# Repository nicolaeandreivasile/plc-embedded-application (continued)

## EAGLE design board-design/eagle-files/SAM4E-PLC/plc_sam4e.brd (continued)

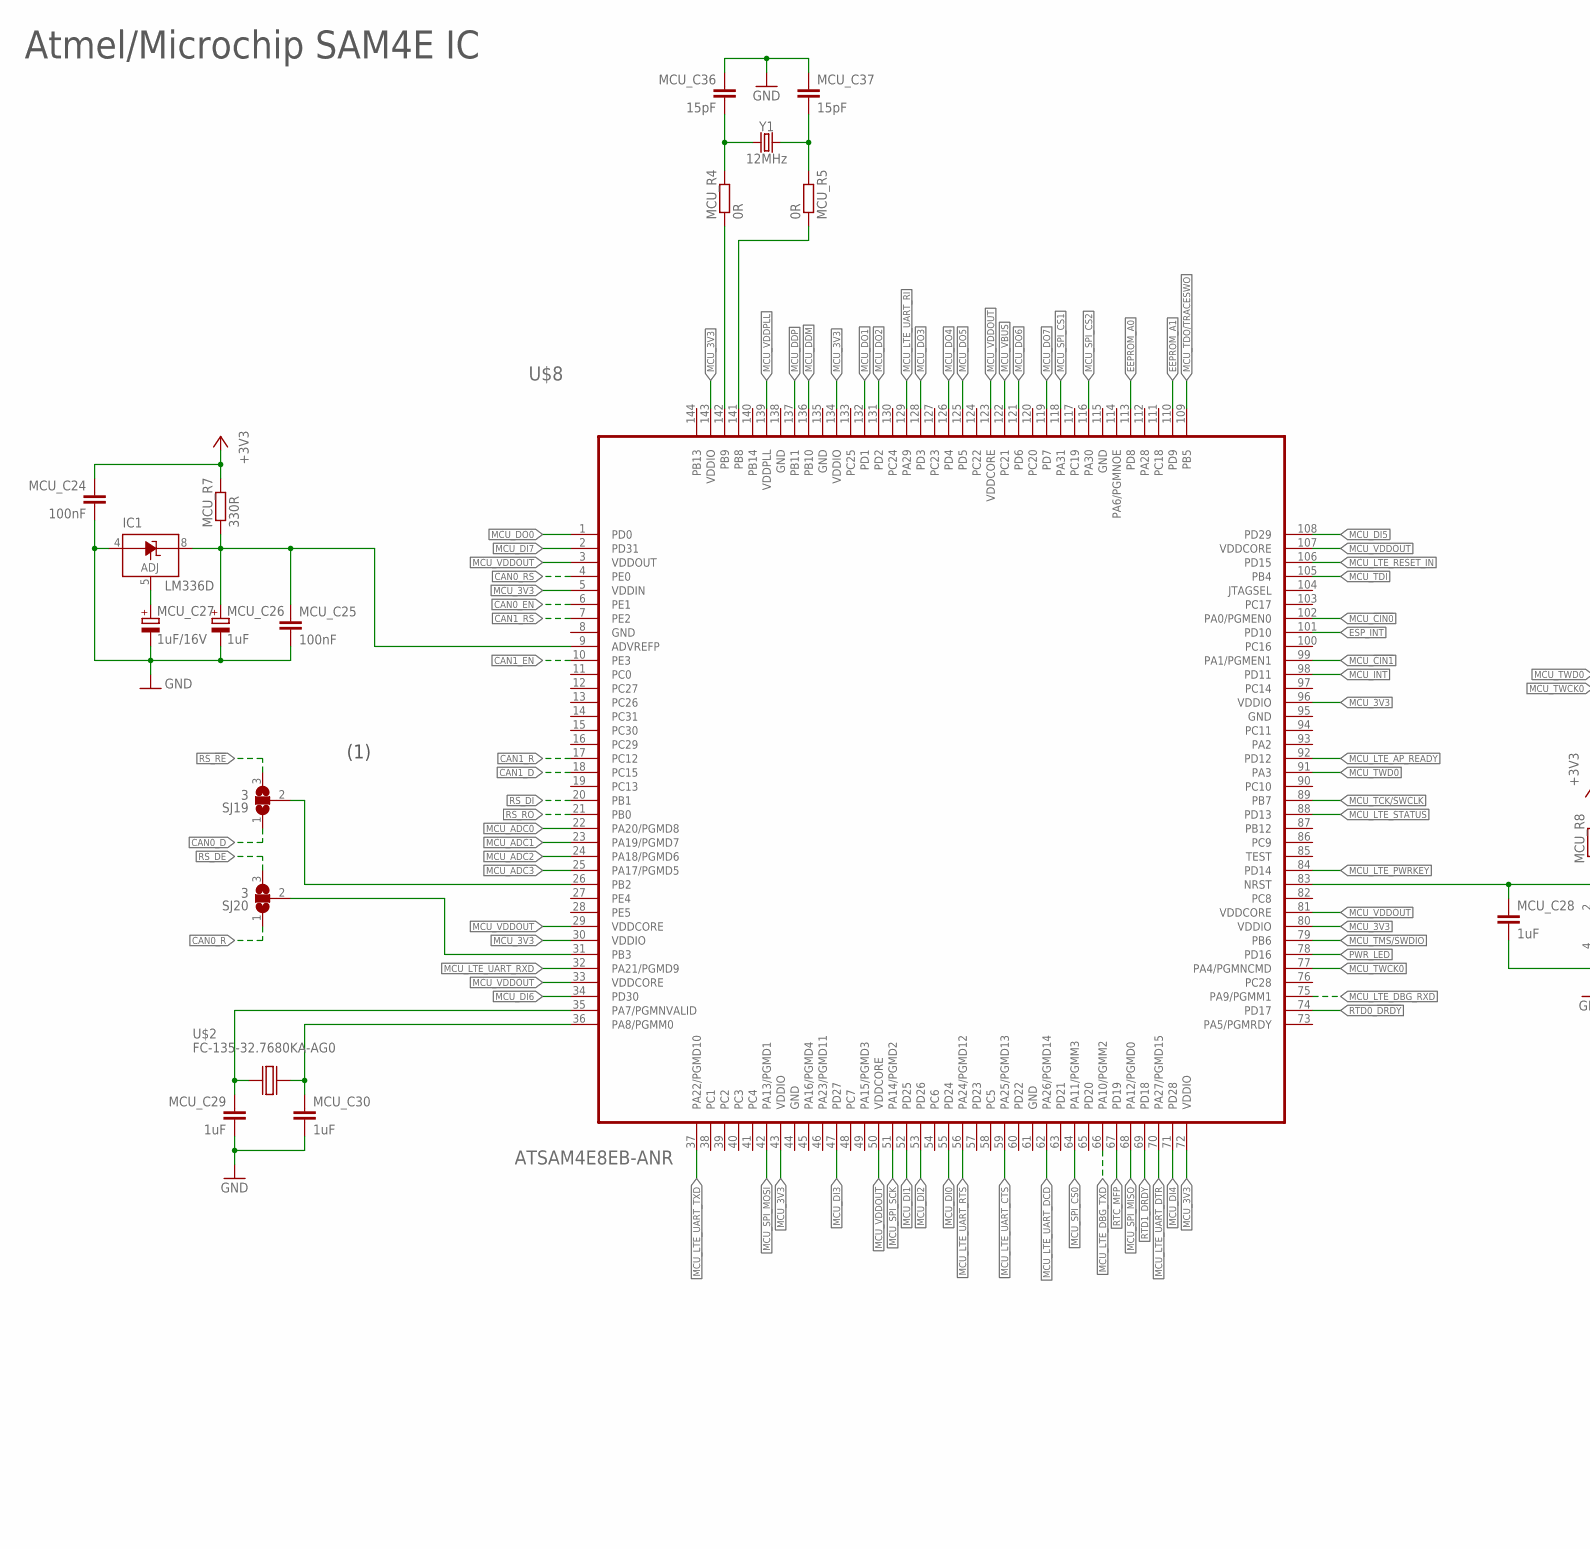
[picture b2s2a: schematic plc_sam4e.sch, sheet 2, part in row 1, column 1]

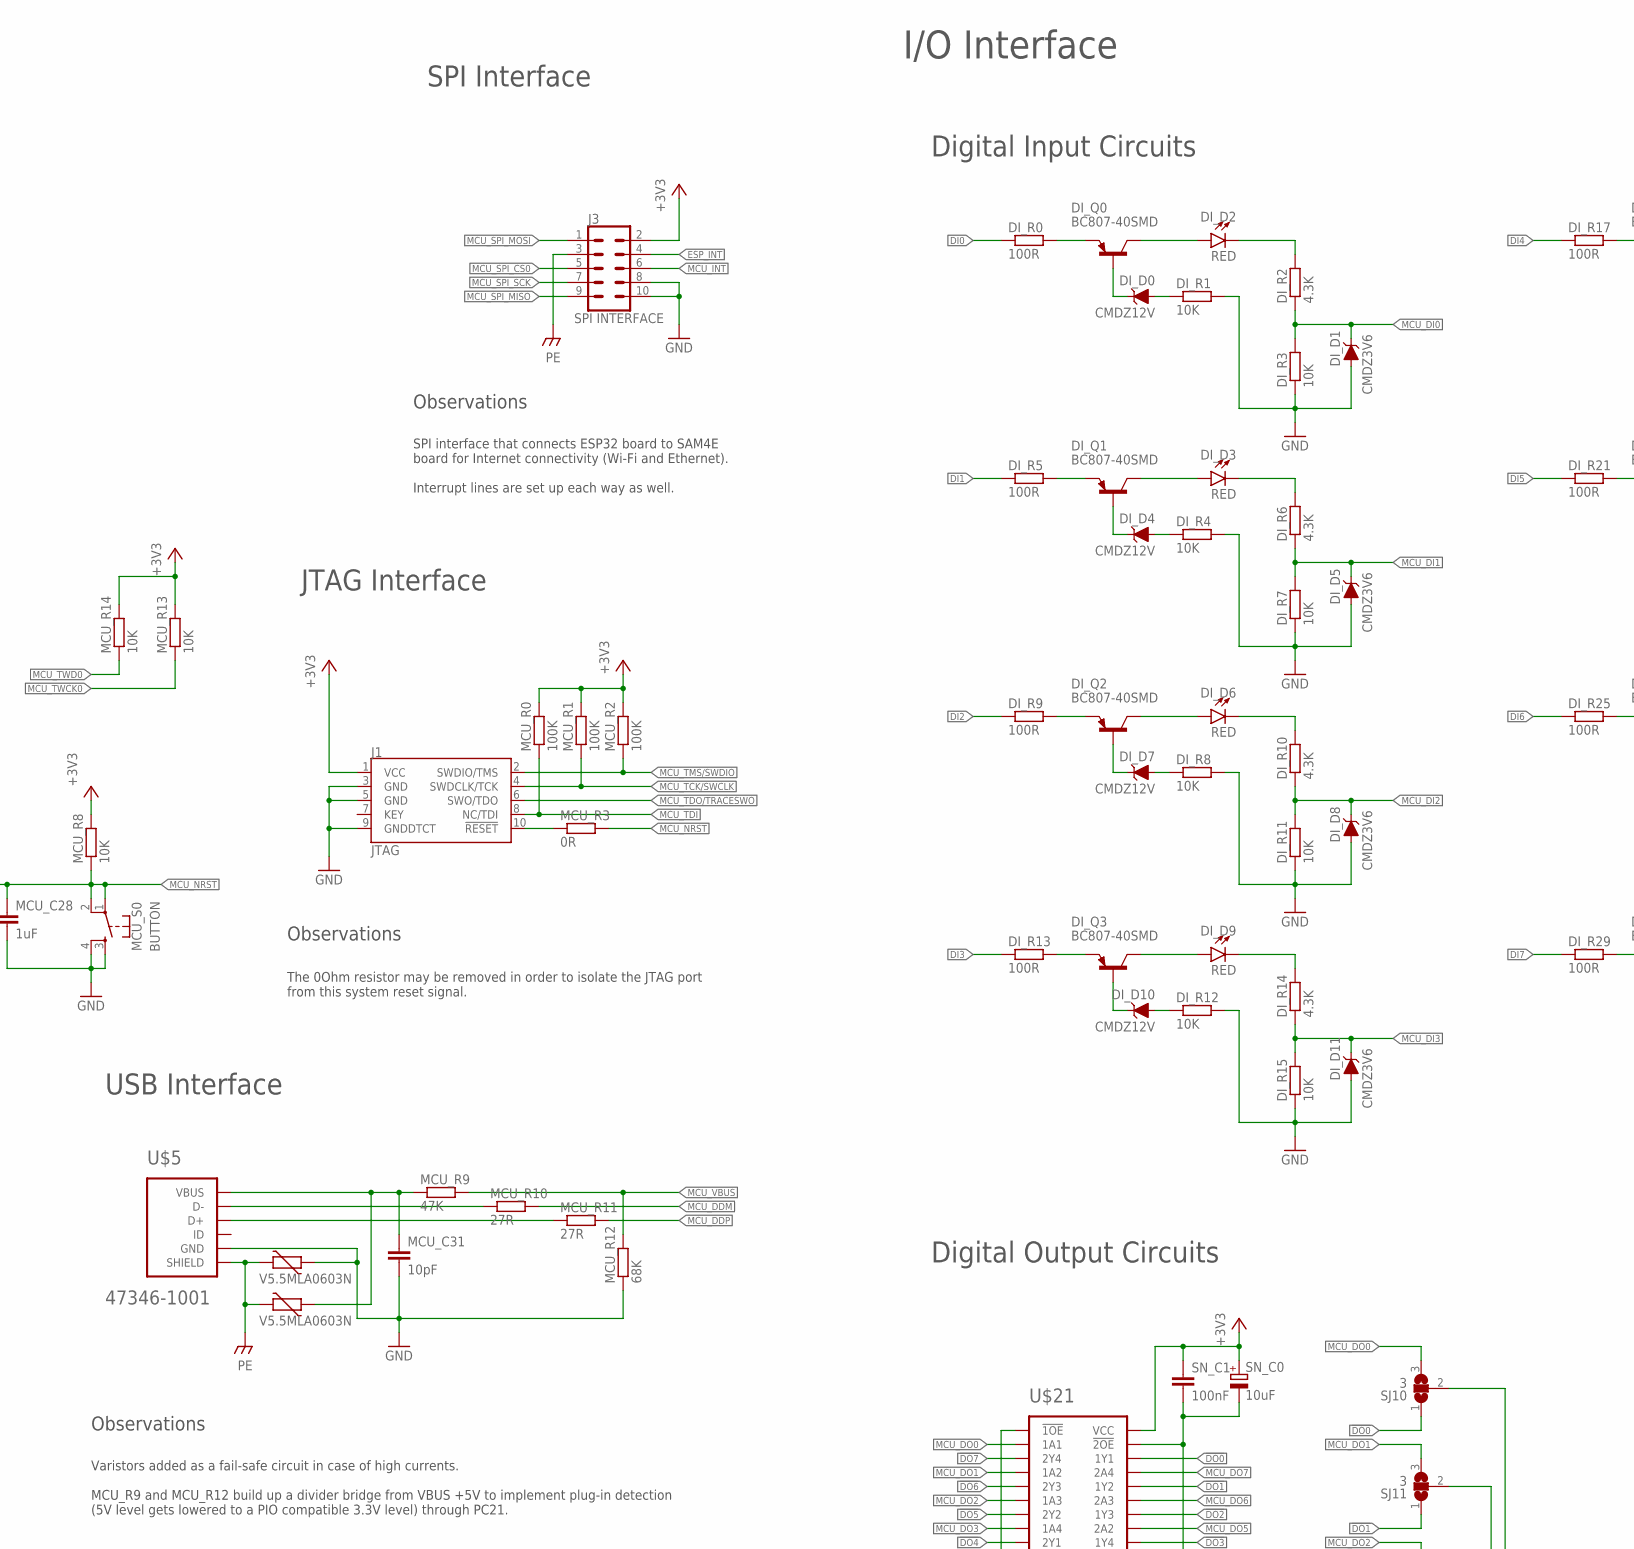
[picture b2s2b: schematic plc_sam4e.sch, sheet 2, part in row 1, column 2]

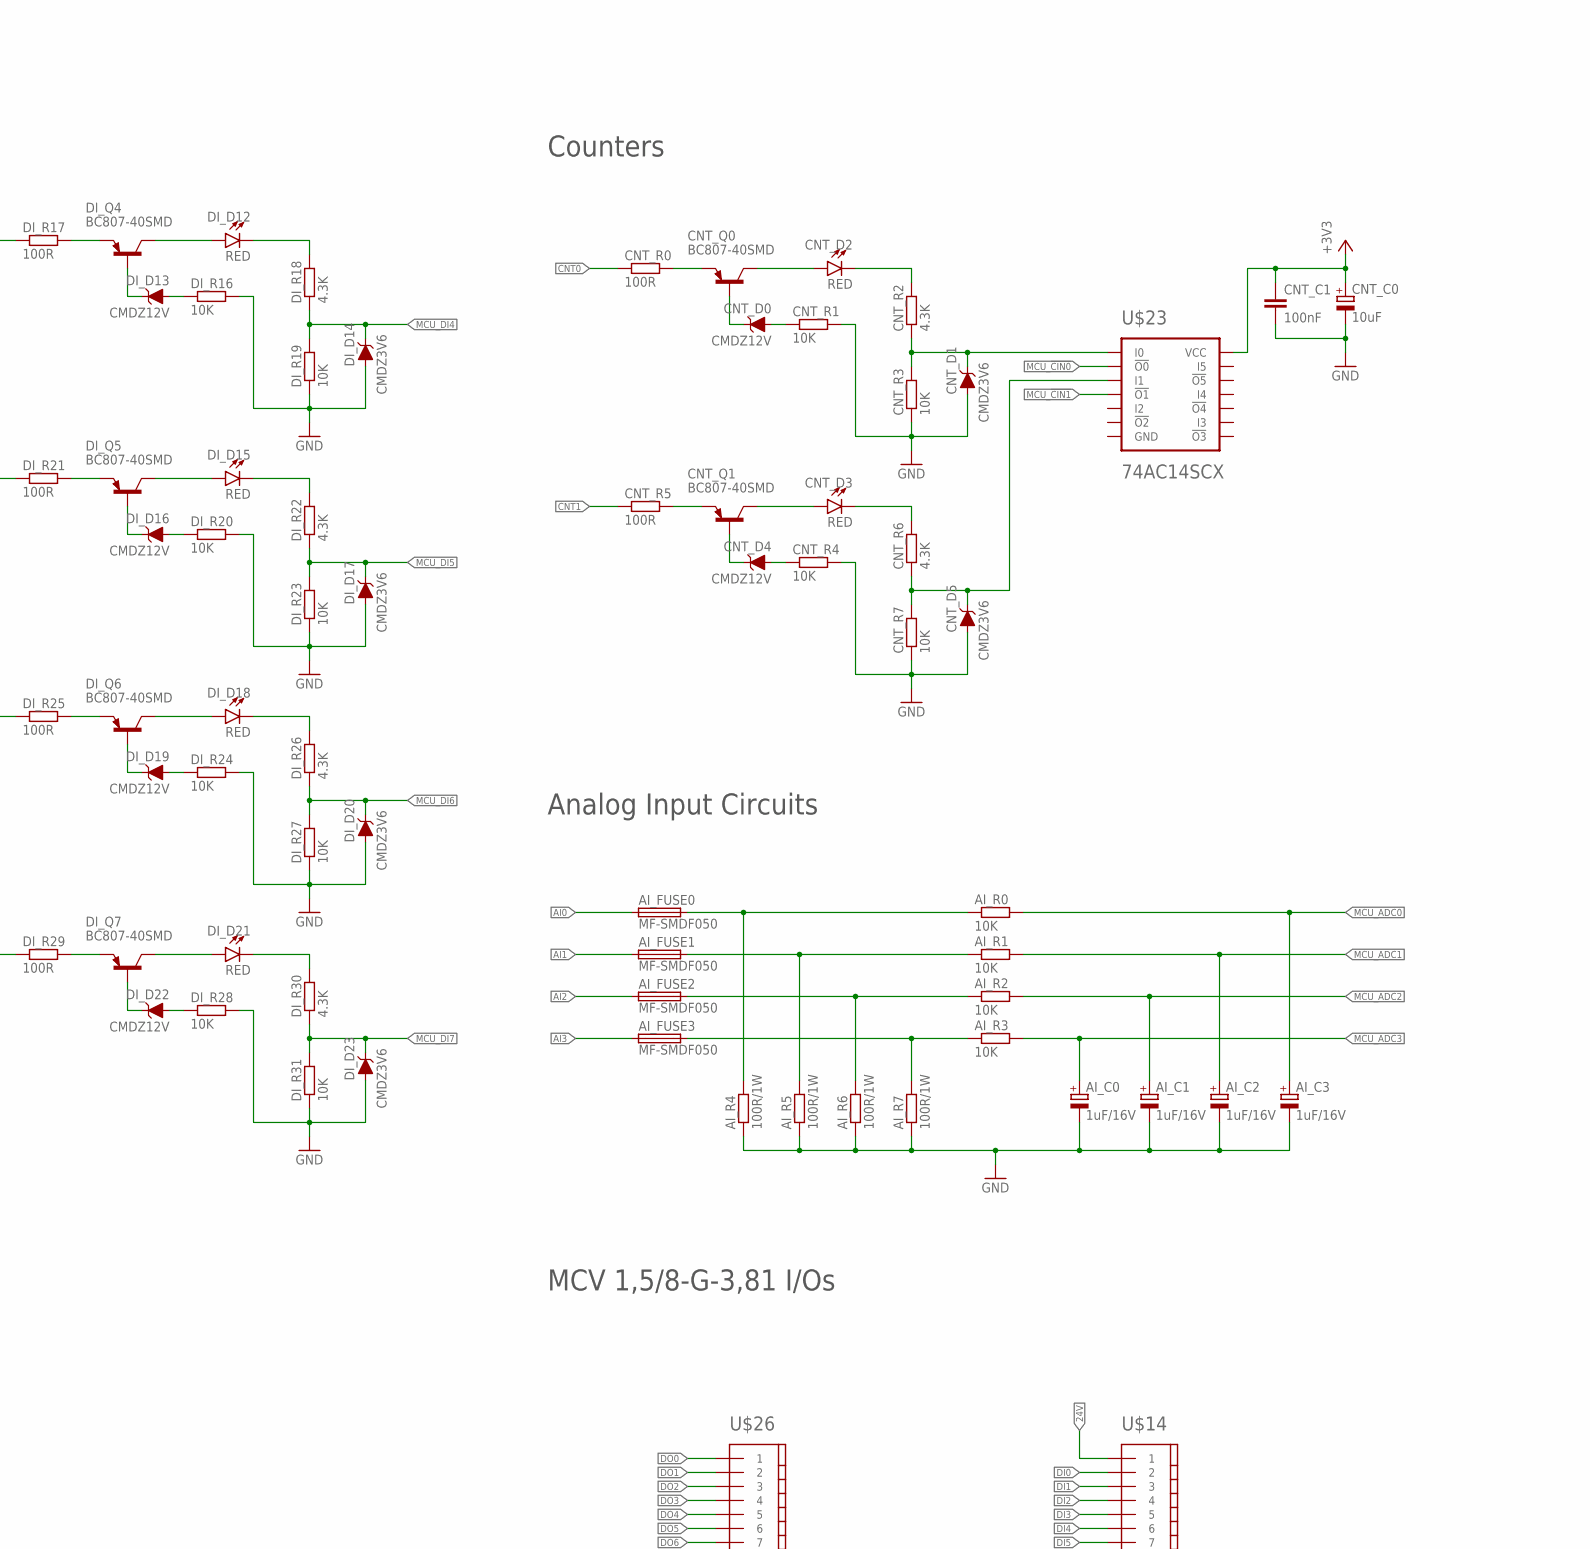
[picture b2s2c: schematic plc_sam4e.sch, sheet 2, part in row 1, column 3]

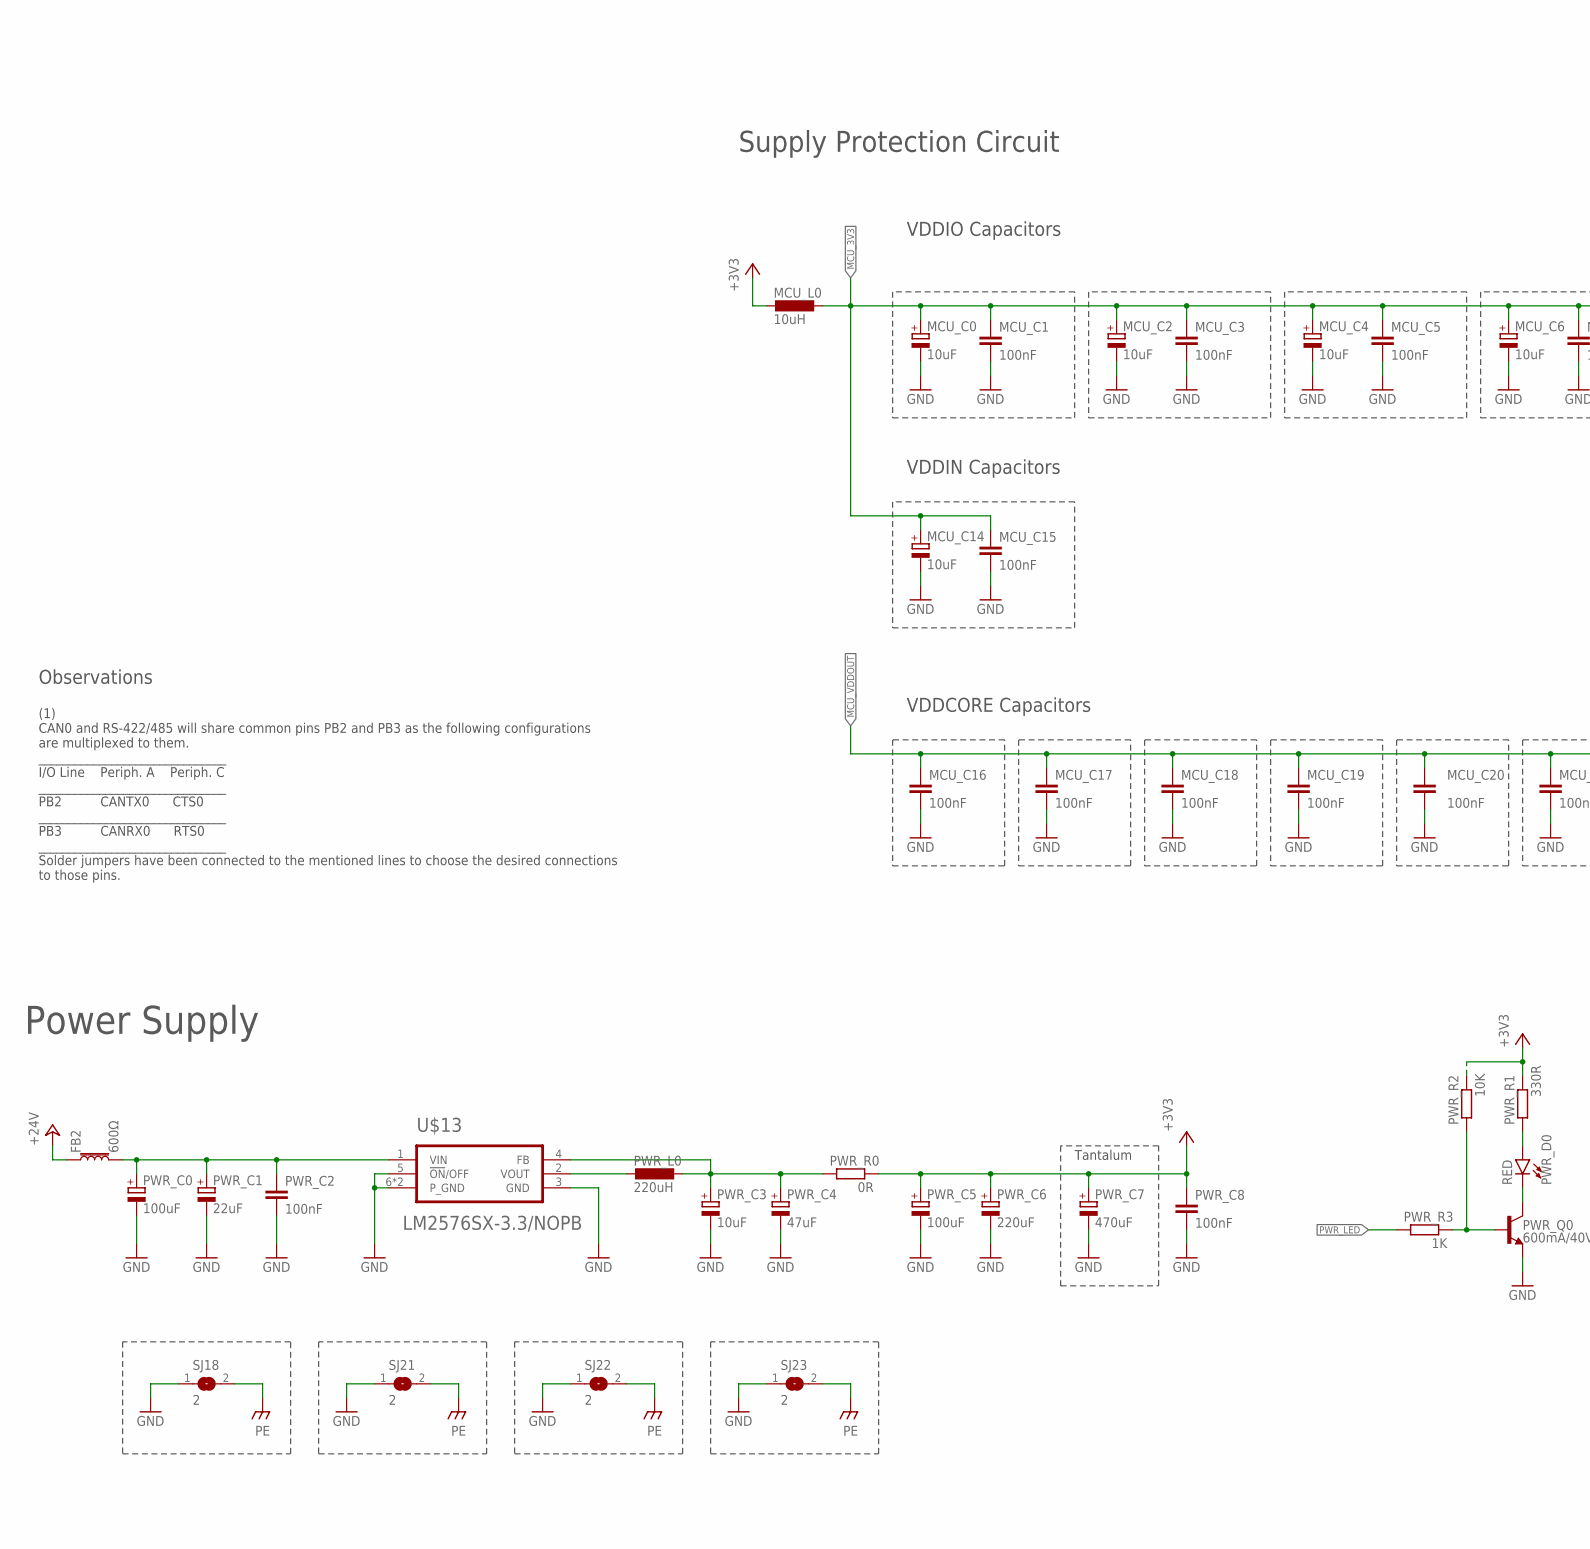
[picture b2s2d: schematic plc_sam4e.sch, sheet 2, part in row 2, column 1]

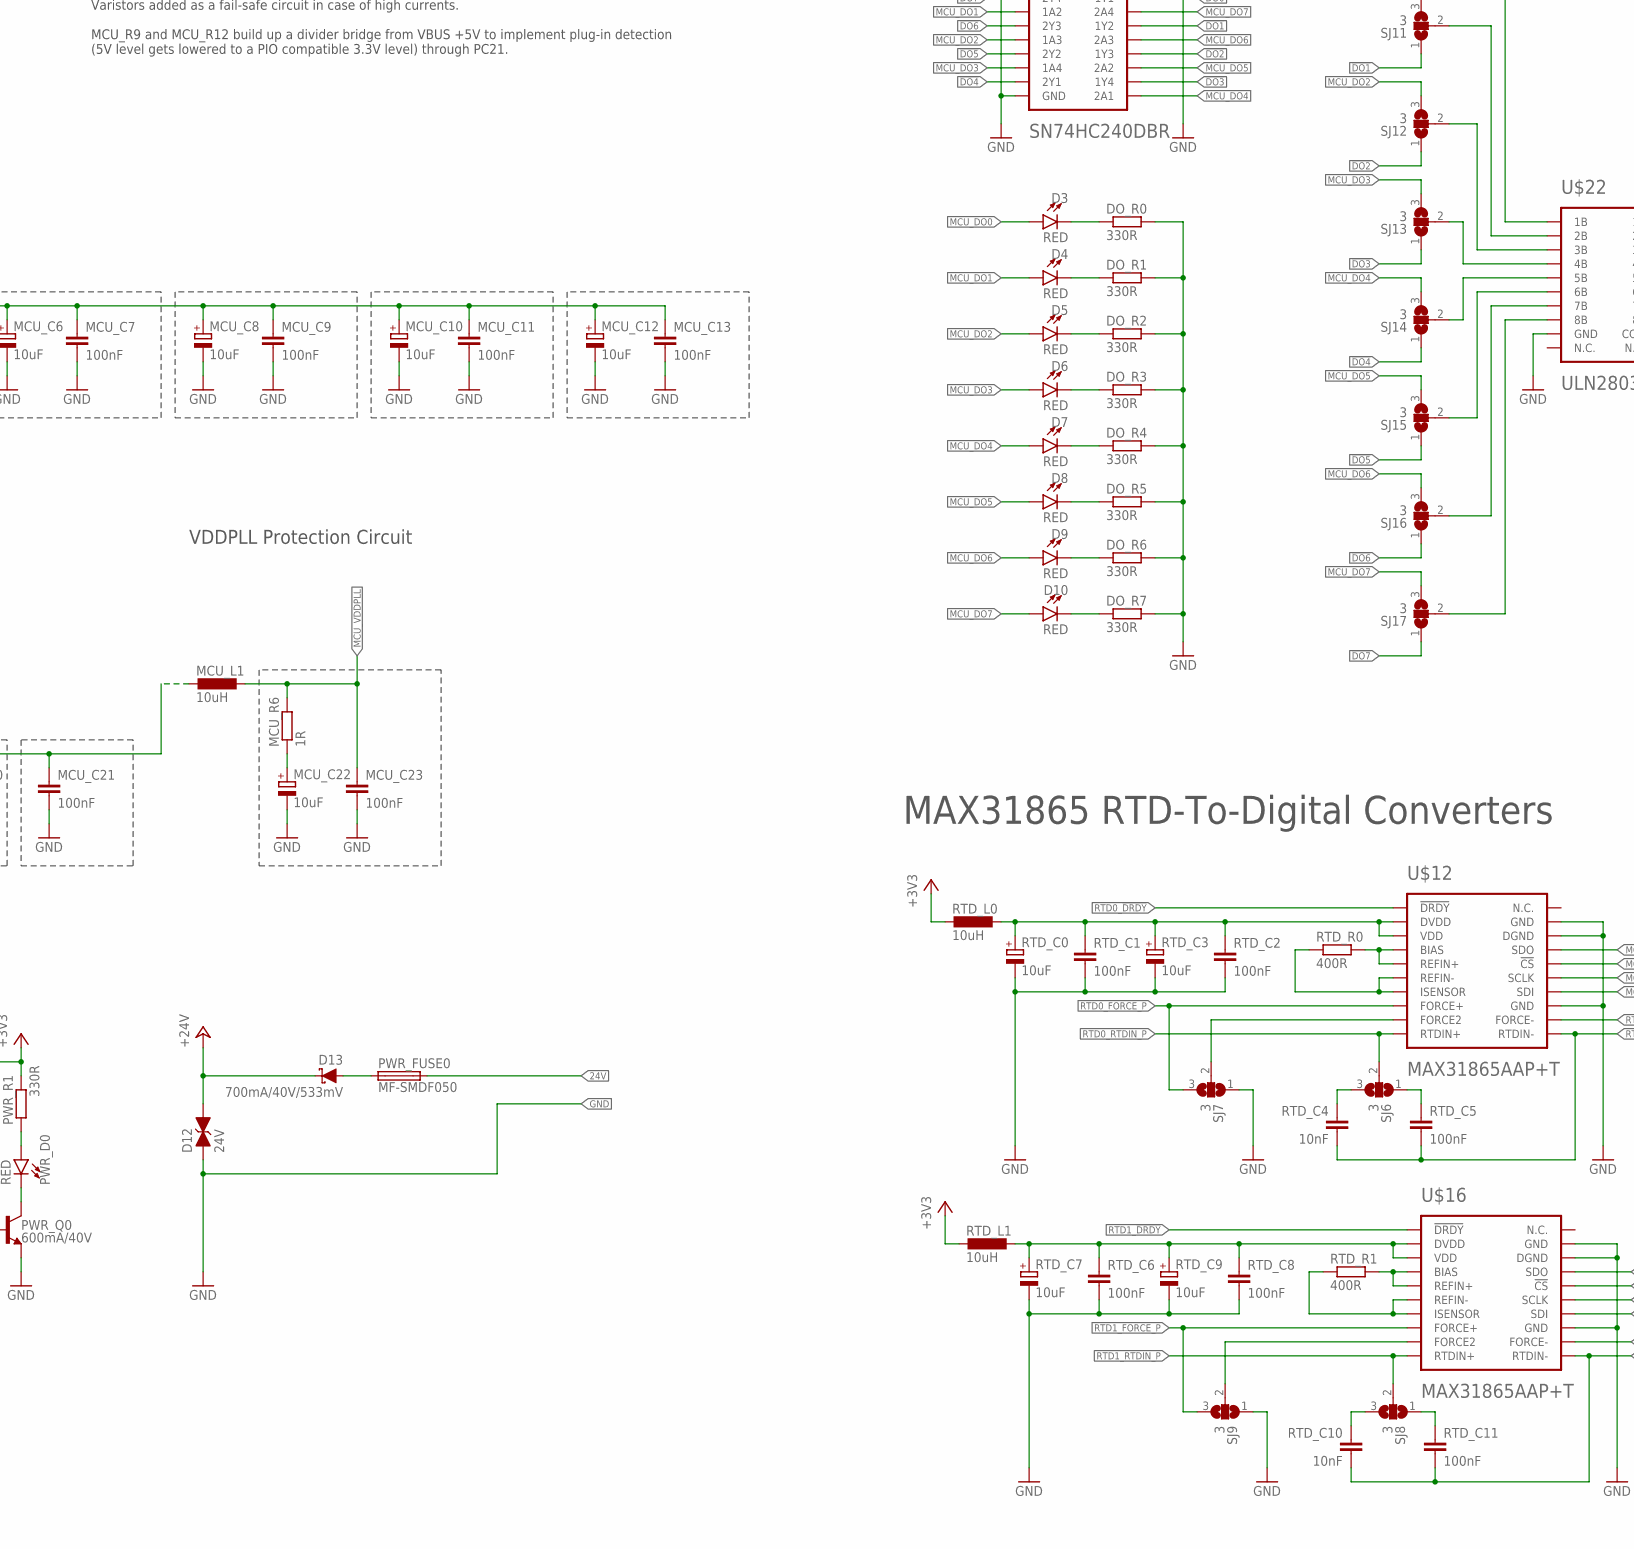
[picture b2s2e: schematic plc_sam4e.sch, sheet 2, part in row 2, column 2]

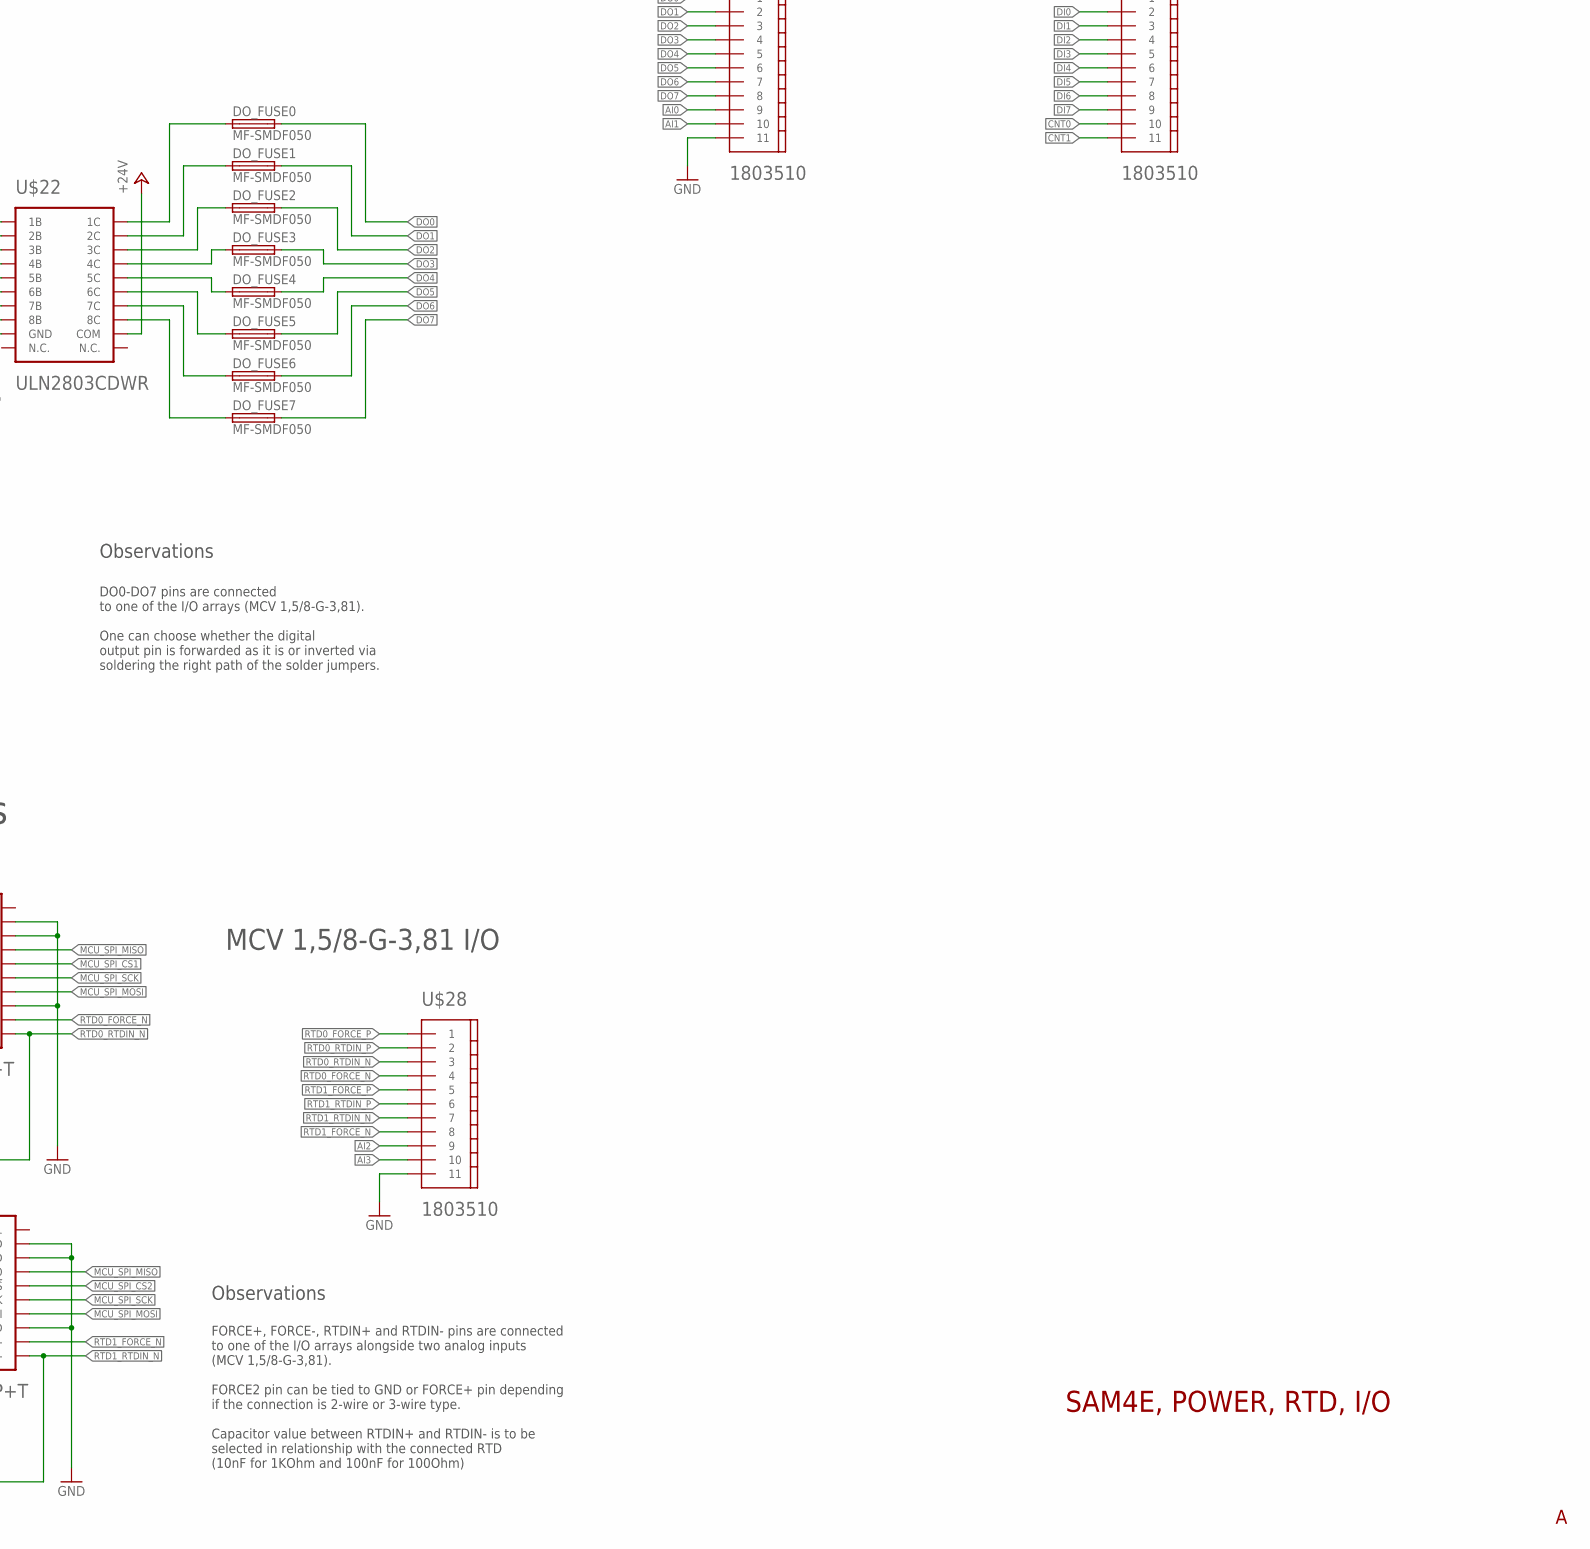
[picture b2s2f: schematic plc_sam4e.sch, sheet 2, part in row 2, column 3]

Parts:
AI_C0, AI_C1, AI_C2, AI_C3: 1uF/16V; SMC_B
AI_FUSE0, AI_FUSE1, AI_FUSE2, AI_FUSE3: MF-SMDF050
AI_R0, AI_R1, AI_R2, AI_R3: 10K; R0402
AI_R4, AI_R5, AI_R6, AI_R7: 100R/1W; R0402
CNT_C0: 10uF; SMC_B
CNT_C1: 100nF; C0402
CNT_D0, CNT_D4: CMDZ12V; SOD-323
CNT_D1, CNT_D5: CMDZ3V6; SOD-323
CNT_D2, CNT_D3: RED; LED-1206
CNT_Q0, CNT_Q1: BC807-40SMD; SOT23-BEC
CNT_R0, CNT_R5: 100R; R0402
CNT_R1, CNT_R3, CNT_R4, CNT_R7: 10K; R0402
CNT_R2, CNT_R6: 4.3K; R0402
D3, D4, D5, D6, D7, D8, D9, D10: RED; LED-1206
D12: 24V; 0603
D13: 700mA/40V/533mV; SOT23-3
DI_D0, DI_D4, DI_D7, DI_D10, DI_D13, DI_D16, DI_D19, DI_D22: CMDZ12V; SOD-323
DI_D1, DI_D5, DI_D8, DI_D11, DI_D14, DI_D17, DI_D20, DI_D23: CMDZ3V6; SOD-323
DI_D2, DI_D3, DI_D6, DI_D9, DI_D12, DI_D15, DI_D18, DI_D21: RED; LED-1206
DI_Q0, DI_Q1, DI_Q2, DI_Q3, DI_Q4, DI_Q5, DI_Q6, DI_Q7: BC807-40SMD; SOT23-BEC
DI_R0, DI_R5, DI_R9, DI_R13, DI_R17, DI_R21, DI_R25, DI_R29: 100R; R0402
DI_R1, DI_R3, DI_R4, DI_R7, DI_R8, DI_R11, DI_R12, DI_R15, DI_R16, DI_R19, DI_R20, DI_R23, DI_R24, DI_R27, DI_R28, DI_R31: 10K; R0402
DI_R2, DI_R6, DI_R10, DI_R14, DI_R18, DI_R22, DI_R26, DI_R30: 4.3K; R0402
DO_FUSE0, DO_FUSE1, DO_FUSE2, DO_FUSE3, DO_FUSE4, DO_FUSE5, DO_FUSE6, DO_FUSE7: MF-SMDF050
DO_R0, DO_R1, DO_R2, DO_R3, DO_R4, DO_R5, DO_R6, DO_R7: 330R; R0402
FB2: 600Ω; 0805
IC1: LM336D; SO08
J1: JTAG; 2X5-SMD-UNSHROUDED
J3: SPI INTERFACE; 2X5-SHROUDED_SMD
MCU_C0, MCU_C2, MCU_C4, MCU_C6, MCU_C8, MCU_C10, MCU_C12, MCU_C14, MCU_C22: 10uF; SMC_B
MCU_C1, MCU_C3, MCU_C5, MCU_C7, MCU_C9, MCU_C11, MCU_C13, MCU_C15, MCU_C16, MCU_C17, MCU_C18, MCU_C19, MCU_C20, MCU_C21, MCU_C23, MCU_C24, MCU_C25: 100nF; C0402
MCU_C26: 1uF; SMC_B
MCU_C27: 1uF/16V; SMC_B
MCU_C28, MCU_C29, MCU_C30: 1uF; C0402
MCU_C31: 10pF; C0402
MCU_C36, MCU_C37: 15pF; C0402
MCU_L0, MCU_L1: 10uH; L1812
MCU_R0, MCU_R1, MCU_R2: 100K; R0402
MCU_R3, MCU_R4, MCU_R5: 0R; R0402
MCU_R6: 1R; R0402
MCU_R7: 330R; R0402
MCU_R8, MCU_R13, MCU_R14: 10K; R0402
MCU_R9: 47K; R0402
MCU_R10, MCU_R11: 27R; R0402
MCU_R12: 68K; R0402
MCU_S0: BUTTON; TACTILE_SWITCH_SMD_4.6X2.8MM
MCU_VAR0, MCU_VAR1: V5.5MLA0603N; CT/CN0603
PWR_C0, PWR_C5: 100uF; SMC_B
PWR_C1: 22uF; SMC_B
PWR_C2, PWR_C8: 100nF; C0402
PWR_C3: 10uF; SMC_B
PWR_C4: 47uF; SMC_B
PWR_C6: 220uF; SMC_B
PWR_C7: 470uF; SMC_B
PWR_D0: RED; LED-1206
PWR_FUSE0: MF-SMDF050
PWR_L0: 220uH; L1812
PWR_Q0: 600mA/40V; SOT23-3
PWR_R0: 0R; R0402
PWR_R1: 330R; R0402
PWR_R2: 10K; R0402
PWR_R3: 1K; R0402
RTD_C0, RTD_C3, RTD_C7, RTD_C9: 10uF; SMC_B
RTD_C1, RTD_C2, RTD_C5, RTD_C6, RTD_C8, RTD_C11: 100nF; C0402
RTD_C4, RTD_C10: 10nF; C0402
RTD_L0, RTD_L1: 10uH; L1812
RTD_R0, RTD_R1: 400R; R0402
SJ6, SJ7, SJ8, SJ9, SJ10, SJ11, SJ12, SJ13, SJ14, SJ15, SJ16, SJ17, SJ19, SJ20: 3; SJ_2
SJ18, SJ21, SJ22, SJ23: 2; SJ
SN_C0: 10uF; SMC_B
SN_C1: 100nF; C0402
U$2: FC-135-32.7680KA-AG0; 3.2X1.5MM
U$5: 47346-1001
U$8: ATSAM4E8EB-ANR; LQFP-144
U$12, U$16: MAX31865AAP+T; TSSOP-20
U$13: LM2576SX-3.3/NOPB; TO-263-5
U$14, U$26, U$28: 1803510
U$21: SN74HC240DBR; SSOP-20
U$22: ULN2803CDWR; SOIC-20
U$23: 74AC14SCX; SOIC-14
Y1: 12MHz; CRYSTAL-SMD-3.2X2.5MM

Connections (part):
24V: PWR_FUSE0.2, U$14.1; also elsewhere on the board
!DO0: SJ10.1, U$21.18 (1Y1)
!DO1: SJ11.1, U$21.16 (1Y2)
!DO2: SJ12.1, U$21.14 (1Y3)
!DO3: SJ13.1, U$21.12 (1Y4)
!DO4: SJ14.1, U$21.9 (2Y1)
!DO5: SJ15.1, U$21.7 (2Y2)
!DO6: SJ16.1, U$21.5 (2Y3)
!DO7: SJ17.1, U$21.3 (2Y4)
+3V3: CNT_C0.+, CNT_C1.1, J1.1 (VCC), J3.2, MCU_C24.1, MCU_L0.2, MCU_R0.2, MCU_R1.2, MCU_R2.2, MCU_R7.2, MCU_R8.2, MCU_R13.2, MCU_R14.2, PWR_C5.+, PWR_C6.+, PWR_C7.+, PWR_C8.1, PWR_R0.2, PWR_R1.2, PWR_R2.2, RTD_L0.2, RTD_L1.2, SN_C0.+, SN_C1.1, U$21.20 (VCC), U$23.14 (VCC); also elsewhere on the board
+24V: D12.2 (C), D13.3 (C), FB2.1, U$22.12 (COM)
AI0: AI_FUSE0.1, U$26.9
AI1: AI_FUSE1.1, U$26.10
AI2: AI_FUSE2.1, U$28.9
AI3: AI_FUSE3.1, U$28.10
CAN0_D: SJ19.1; also elsewhere on the board
CAN0_EN: U$8.6 (PE1); also elsewhere on the board
CAN0_R: SJ20.1; also elsewhere on the board
CAN0_RS: U$8.4 (PE0); also elsewhere on the board
CAN1_D: U$8.18 (PC15); also elsewhere on the board
CAN1_EN: U$8.10 (PE3); also elsewhere on the board
CAN1_R: U$8.17 (PC12); also elsewhere on the board
CAN1_RS: U$8.7 (PE2); also elsewhere on the board
CNT0: CNT_R0.1, U$14.10
CNT1: CNT_R5.1, U$14.11
DI0: DI_R0.1, U$14.2
DI1: DI_R5.1, U$14.3
DI2: DI_R9.1, U$14.4
DI3: DI_R13.1, U$14.5
DI4: DI_R17.1, U$14.6
DI5: DI_R21.1, U$14.7
DI6: DI_R25.1, U$14.8
DI7: DI_R29.1, U$14.9
DO0: DO_FUSE0.2, U$26.1
DO1: DO_FUSE1.2, U$26.2
DO2: DO_FUSE2.2, U$26.3
DO3: DO_FUSE3.2, U$26.4
DO4: DO_FUSE4.2, U$26.5
DO5: DO_FUSE5.2, U$26.6
DO6: DO_FUSE6.2, U$26.7
DO7: DO_FUSE7.2, U$26.8
EEPROM_A0: U$8.113 (PD8); also elsewhere on the board
EEPROM_A1: U$8.110 (PD9); also elsewhere on the board
ESP_INT: J3.4, U$8.101 (PD10)
GND: AI_C0.-, AI_C1.-, AI_C2.-, AI_C3.-, AI_R4.1, AI_R5.1, AI_R6.1, AI_R7.1, CNT_C0.-, CNT_C1.2, CNT_D1.A, CNT_D5.A, CNT_R1.2, CNT_R3.1, CNT_R4.2, CNT_R7.1, D12.1 (A), DI_D1.A, DI_D5.A, DI_D8.A, DI_D11.A, DI_D14.A, DI_D17.A, DI_D20.A, DI_D23.A, DI_R1.2, DI_R3.1, DI_R4.2, DI_R7.1, DI_R8.2, DI_R11.1, DI_R12.2, DI_R15.1, DI_R16.2, DI_R19.1, DI_R20.2, DI_R23.1, DI_R24.2, DI_R27.1, DI_R28.2, DI_R31.1, DO_R0.2, DO_R1.2, DO_R2.2, DO_R3.2, DO_R4.2, DO_R5.2, DO_R6.2, DO_R7.2, IC1.4 (A), J1.3 (GND), J1.5 (GND), J1.9 (GNDDTCT), J3.8, J3.10, MCU_C0.-, MCU_C1.2, MCU_C2.-, MCU_C3.2, MCU_C4.-, MCU_C5.2, MCU_C6.-, MCU_C7.2, MCU_C8.-, MCU_C9.2, MCU_C10.-, MCU_C11.2, MCU_C12.-, MCU_C13.2, MCU_C14.-, MCU_C15.2, MCU_C16.2, MCU_C17.2, MCU_C18.2, MCU_C19.2, MCU_C20.2, MCU_C21.2, MCU_C22.-, MCU_C23.2, MCU_C24.2, MCU_C25.2, MCU_C26.-, MCU_C27.-, MCU_C28.2, MCU_C29.2, MCU_C30.2, MCU_C31.2, MCU_C36.1, MCU_C37.1, MCU_R12.1, MCU_S0.3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; also elsewhere on the board
MCU_3V3: MCU_C0.+, MCU_C1.1, MCU_C2.+, MCU_C3.1, MCU_C4.+, MCU_C5.1, MCU_C6.+, MCU_C7.1, MCU_C8.+, MCU_C9.1, MCU_C10.+, MCU_C11.1, MCU_C12.+, MCU_C13.1, MCU_C14.+, MCU_C15.1, MCU_L0.1, U$8.5 (VDDIN), U$8.30 (VDDIO), U$8.43 (VDDIO), U$8.72 (VDDIO), U$8.80 (VDDIO), U$8.96 (VDDIO), U$8.134 (VDDIO), U$8.143 (VDDIO)
MCU_!CIN0: U$8.102 (PA0/PGMEN0), U$23.2 (!O0)
MCU_!CIN1: U$8.99 (PA1/PGMEN1), U$23.4 (!O1)
MCU_ADC0: AI_C3.+, AI_R0.2, U$8.22 (PA20/PGMD8)
MCU_ADC1: AI_C2.+, AI_R1.2, U$8.23 (PA19/PGMD7)
MCU_ADC2: AI_C1.+, AI_R2.2, U$8.24 (PA18/PGMD6)
MCU_ADC3: AI_C0.+, AI_R3.2, U$8.25 (PA17/PGMD5)
MCU_ADVREFP: IC1.8 (C), MCU_C25.1, MCU_C26.+, MCU_R7.1, U$8.9 (ADVREFP)
MCU_DDM: MCU_R10.2, U$8.136 (PB10)
MCU_DDP: MCU_R11.2, U$8.137 (PB11)
MCU_DI0: DI_D1.C, DI_R2.1, DI_R3.2, U$8.55 (PD24)
MCU_DI1: DI_D5.C, DI_R6.1, DI_R7.2, U$8.52 (PD25)
MCU_DI2: DI_D8.C, DI_R10.1, DI_R11.2, U$8.53 (PD26)
MCU_DI3: DI_D11.C, DI_R14.1, DI_R15.2, U$8.47 (PD27)
MCU_DI4: DI_D14.C, DI_R18.1, DI_R19.2, U$8.71 (PD28)
MCU_DI5: DI_D17.C, DI_R22.1, DI_R23.2, U$8.108 (PD29)
MCU_DI6: DI_D20.C, DI_R26.1, DI_R27.2, U$8.34 (PD30)
MCU_DI7: DI_D23.C, DI_R30.1, DI_R31.2, U$8.2 (PD31)
MCU_DO0: D3.A, SJ10.3, U$8.1 (PD0), U$21.2 (1A1)
MCU_DO1: D4.A, SJ11.3, U$8.132 (PD1), U$21.4 (1A2)
MCU_DO2: D5.A, SJ12.3, U$8.131 (PD2), U$21.6 (1A3)
MCU_DO3: D6.A, SJ13.3, U$8.128 (PD3), U$21.8 (1A4)
MCU_DO4: D7.A, SJ14.3, U$8.126 (PD4), U$21.11 (2A1)
MCU_DO5: D8.A, SJ15.3, U$8.125 (PD5), U$21.13 (2A2)
MCU_DO6: D9.A, SJ16.3, U$8.121 (PD6), U$21.15 (2A3)
MCU_DO7: D10.A, SJ17.3, U$8.119 (PD7), U$21.17 (2A4)
MCU_INT: J3.6, U$8.98 (PD11)
MCU_LTE_AP_READY: U$8.92 (PD12); also elsewhere on the board
MCU_LTE_DBG_RXD: U$8.75 (PA9/PGMM1); also elsewhere on the board
MCU_LTE_DBG_TXD: U$8.66 (PA10/PGMM2); also elsewhere on the board
MCU_LTE_PWRKEY: U$8.84 (PD14); also elsewhere on the board
MCU_LTE_RESET_IN: U$8.106 (PD15); also elsewhere on the board
MCU_LTE_STATUS: U$8.88 (PD13); also elsewhere on the board
MCU_LTE_UART_CTS: U$8.59 (PA25/PGMD13); also elsewhere on the board
MCU_LTE_UART_DCD: U$8.62 (PA26/PGMD14); also elsewhere on the board
MCU_LTE_UART_DTR: U$8.70 (PA27/PGMD15); also elsewhere on the board
MCU_LTE_UART_RI: U$8.129 (PA29); also elsewhere on the board
MCU_LTE_UART_RTS: U$8.56 (PA24/PGMD12); also elsewhere on the board
MCU_LTE_UART_RXD: U$8.32 (PA21/PGMD9); also elsewhere on the board
MCU_LTE_UART_TXD: U$8.37 (PA22/PGMD10); also elsewhere on the board
MCU_NRST: MCU_C28.1, MCU_R3.2, MCU_R8.1, MCU_S0.1, MCU_S0.2, U$8.83 (NRST)
MCU_SPI_CS0: J3.5, U$8.64 (PA11/PGMM3)
MCU_SPI_CS1: U$8.118 (PA31), U$12.16 (!CS)
MCU_SPI_CS2: U$8.116 (PA30), U$16.16 (!CS)
MCU_SPI_MISO: J3.9, U$8.68 (PA12/PGMD0), U$12.17 (SDO), U$16.17 (SDO)
MCU_SPI_MOSI: J3.1, U$8.42 (PA13/PGMD1), U$12.14 (SDI), U$16.14 (SDI)
MCU_SPI_SCK: J3.7, U$8.51 (PA14/PGMD2), U$12.15 (SCLK), U$16.15 (SCLK)
MCU_TCK/SWCLK: J1.4 (SWDCLK/TCK), MCU_R1.1, U$8.89 (PB7)
MCU_TDI: J1.8 (NC/TDI), MCU_R0.1, U$8.105 (PB4)
MCU_TDO/TRACESWO: J1.6 (SWO/TDO), U$8.109 (PB5)
MCU_TMS/SWDIO: J1.2 (SWDIO/TMS), MCU_R2.1, U$8.79 (PB6)
MCU_TWCK0: MCU_R13.1, U$8.77 (PA4/PGMNCMD); also elsewhere on the board
MCU_TWD0: MCU_R14.1, U$8.91 (PA3); also elsewhere on the board
MCU_VBUS: MCU_R9.2, MCU_R12.2, U$8.122 (PC21)
MCU_VDDOUT: MCU_C16.1, MCU_C17.1, MCU_C18.1, MCU_C19.1, MCU_C20.1, MCU_C21.1, MCU_L1.2, U$8.3 (VDDOUT), U$8.29 (VDDCORE), U$8.33 (VDDCORE), U$8.50 (VDDCORE), U$8.81 (VDDCORE), U$8.107 (VDDCORE), U$8.123 (VDDCORE)
MCU_VDDPLL: MCU_C23.1, MCU_L1.1, MCU_R6.2, U$8.139 (VDDPLL)
unnamed: D13.1 (A), PWR_FUSE0.1
unnamed: PWR_Q0.1 (B), PWR_R2.1, PWR_R3.2
unnamed: IC1.5 (ADJ), MCU_C27.+
unnamed: PWR_D0.A, PWR_R1.1
unnamed: PWR_L0.2, U$13.2 (VOUT)
unnamed: FB2.2, PWR_C0.+, PWR_C1.+, PWR_C2.1, U$13.1 (VIN)
unnamed: PWR_C3.+, PWR_C4.+, PWR_L0.1, PWR_R0.1, U$13.4 (FB)
unnamed: PWR_D0.C, PWR_Q0.3 (C)
unnamed: SJ20.2, U$8.31 (PB3)
unnamed: MCU_R5.1, U$8.141 (PB8)
unnamed: SJ7.2, U$12.9 (FORCE2)
unnamed: MCU_C31.1, MCU_R9.1, MCU_VAR1.1, U$5.1 (VBUS)
unnamed: RTD_R1.2, U$16.4 (BIAS), U$16.5 (REFIN+)
unnamed: RTD_C0.+, RTD_C1.1, RTD_C2.1, RTD_C3.+, RTD_L0.1, U$12.2 (DVDD), U$12.3 (VDD)
unnamed: MCU_C22.+, MCU_R6.1
unnamed: RTD_R1.1, U$16.6 (REFIN-), U$16.7 (ISENSOR)
unnamed: RTD_R0.2, U$12.4 (BIAS), U$12.5 (REFIN+)
unnamed: RTD_R0.1, U$12.6 (REFIN-), U$12.7 (ISENSOR)
unnamed: SJ13.2, U$22.4 (4B)
unnamed: SJ14.2, U$22.5 (5B)
unnamed: SJ12.2, U$22.3 (3B)
unnamed: SJ15.2, U$22.6 (6B)
unnamed: AI_FUSE0.2, AI_R0.1, AI_R4.2
unnamed: RTD_C10.1, SJ8.3
unnamed: RTD_C4.1, SJ6.3
unnamed: RTD_C5.1, SJ6.1
unnamed: RTD_C11.1, SJ8.1
unnamed: RTD_C6.1, RTD_C7.+, RTD_C8.1, RTD_C9.+, RTD_L1.1, U$16.2 (DVDD), U$16.3 (VDD)
unnamed: SJ9.2, U$16.9 (FORCE2)
unnamed: AI_FUSE1.2, AI_R1.1, AI_R5.2
unnamed: AI_FUSE2.2, AI_R2.1, AI_R6.2
unnamed: AI_FUSE3.2, AI_R3.1, AI_R7.2
unnamed: SJ16.2, U$22.7 (7B)
unnamed: SJ17.2, U$22.8 (8B)
unnamed: SJ11.2, U$22.2 (2B)
unnamed: SJ10.2, U$22.1 (1B)
unnamed: DO_FUSE0.1, U$22.20 (1C)
unnamed: DO_FUSE1.1, U$22.19 (2C)
unnamed: DO_FUSE2.1, U$22.18 (3C)
unnamed: DO_FUSE3.1, U$22.17 (4C)
unnamed: DO_FUSE4.1, U$22.16 (5C)
unnamed: DO_FUSE5.1, U$22.15 (6C)
unnamed: DO_FUSE6.1, U$22.14 (7C)
unnamed: DO_FUSE7.1, U$22.13 (8C)
unnamed: D3.C, DO_R0.1
unnamed: DI_Q0.E, DI_R0.2
unnamed: DI_D2.A, DI_Q0.C
unnamed: D4.C, DO_R1.1
unnamed: DI_D0.C, DI_Q0.B
unnamed: DI_D0.A, DI_R1.1
unnamed: D5.C, DO_R2.1
unnamed: DI_Q1.E, DI_R5.2
unnamed: DI_D3.A, DI_Q1.C
unnamed: D6.C, DO_R3.1
unnamed: DI_D2.C, DI_R2.2
unnamed: DI_D4.C, DI_Q1.B
unnamed: D7.C, DO_R4.1
unnamed: DI_D4.A, DI_R4.1
unnamed: DI_D3.C, DI_R6.2
unnamed: D8.C, DO_R5.1
unnamed: DI_Q2.E, DI_R9.2
unnamed: DI_D6.A, DI_Q2.C
unnamed: D9.C, DO_R6.1
unnamed: DI_D7.C, DI_Q2.B
unnamed: DI_D7.A, DI_R8.1
unnamed: D10.C, DO_R7.1
unnamed: DI_D6.C, DI_R10.2
unnamed: DI_Q3.E, DI_R13.2
unnamed: DI_D9.A, DI_Q3.C
unnamed: DI_D10.C, DI_Q3.B
unnamed: DI_D10.A, DI_R12.1
unnamed: DI_D9.C, DI_R14.2
unnamed: DI_Q4.E, DI_R17.2
unnamed: DI_D12.A, DI_Q4.C
unnamed: DI_D13.C, DI_Q4.B
unnamed: DI_D13.A, DI_R16.1
unnamed: DI_D12.C, DI_R18.2
unnamed: DI_Q5.E, DI_R21.2
unnamed: DI_D15.A, DI_Q5.C
unnamed: DI_D16.C, DI_Q5.B
unnamed: DI_D16.A, DI_R20.1
unnamed: DI_D15.C, DI_R22.2
unnamed: DI_Q6.E, DI_R25.2
unnamed: DI_D18.A, DI_Q6.C
unnamed: DI_D19.C, DI_Q6.B
unnamed: DI_D19.A, DI_R24.1
unnamed: DI_D18.C, DI_R26.2
unnamed: DI_Q7.E, DI_R29.2
unnamed: DI_D21.A, DI_Q7.C
unnamed: DI_D22.C, DI_Q7.B
unnamed: DI_D22.A, DI_R28.1
unnamed: DI_D21.C, DI_R30.2
unnamed: CNT_Q0.E, CNT_R0.2
unnamed: CNT_D2.A, CNT_Q0.C
unnamed: CNT_D0.C, CNT_Q0.B
unnamed: CNT_D0.A, CNT_R1.1
unnamed: CNT_D2.C, CNT_R2.2
unnamed: CNT_Q1.E, CNT_R5.2
unnamed: CNT_D3.A, CNT_Q1.C
unnamed: CNT_D4.C, CNT_Q1.B
unnamed: CNT_D4.A, CNT_R4.1
unnamed: CNT_D3.C, CNT_R6.2
unnamed: CNT_D1.C, CNT_R2.1, CNT_R3.2, U$23.1 (I0)
unnamed: CNT_D5.C, CNT_R6.1, CNT_R7.2, U$23.3 (I1)
unnamed: J1.10 (!RESET), MCU_R3.1
unnamed: MCU_C36.2, MCU_R4.2, Y1.1
unnamed: MCU_C37.2, MCU_R5.2, Y1.3 (2)
unnamed: MCU_C29.1, U$2.2, U$8.35 (PA7/PGMNVALID)
unnamed: MCU_C30.1, U$2.1, U$8.36 (PA8/PGMM0)
unnamed: MCU_R11.1, U$5.3 (D+)
unnamed: MCU_R10.1, U$5.2 (D-)
unnamed: MCU_R4.1, U$8.142 (PB9)
unnamed: SJ19.2, U$8.26 (PB2)
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
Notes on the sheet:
Tantalum
MAX31865 RTD-To-Digital Converters
Observations
FORCE+, FORCE-, RTDIN+ and RTDIN- pins are connected to one of the I/O arrays alongside two analog inputs (MCV 1,5/8-G-3,81). FORCE2 pin can be tied to GND or FORCE+ pin depending if the connection is 2-wire or 3-wire type. Capacitor value between RTDIN+ and RTDIN- is to be selected in relationship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
MCV 1,5/8-G-3,81 I/O
Digital Output Circuits
Analog Input Circuits
Digital Input Circuits
Counters
I/O Interface
DO0-DO7 pins are connected to one of the I/O arrays (MCV 1,5/8-G-3,81). One can choose whether the digital output pin is forwarded as it is or inverted via soldering the right path of the solder jumpers.
MCV 1,5/8-G-3,81 I/Os
SPI Interface
SPI interface that connects ESP32 board to SAM4E board for Internet connectivity (Wi-Fi and Ethernet). Interrupt lines are set up each way as well.
VDDIO Capacitors
VDDIN Capacitors
VDDCORE Capacitors
VDDPLL Protection Circuit
Supply Protection Circuit
USB Interface
Varistors added as a fail-safe circuit in case of high currents. MCU_R9 and MCU_R12 build up a divider bridge from VBUS +5V to implement plug-in detection (5V level gets lowered to a PIO compatible 3.3V level) through PC21.
Atmel/Microchip SAM4E IC
Power Supply
JTAG Interface
The 0Ohm resistor may be removed in order to isolate the JTAG port from this system reset signal.
(1) CAN0 and RS-422/485 will share common pins PB2 and PB3 as the following configurations are multiplexed to them. _______________________________ I/O Line Periph. A Periph. C _______________________________ PB2 CANTX0 CTS0 _______________________________ PB3 CANRX0 RTS0 __________________________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
(1)
SAM4E, POWER, RTD, I/O

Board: 2 copper layers, 357 parts (0 on the bottom side), 300 nets, no tracks yet.
